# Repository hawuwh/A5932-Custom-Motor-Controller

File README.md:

# Custom Motor Controller using A5932 for LBYEC3H Solar Car Project

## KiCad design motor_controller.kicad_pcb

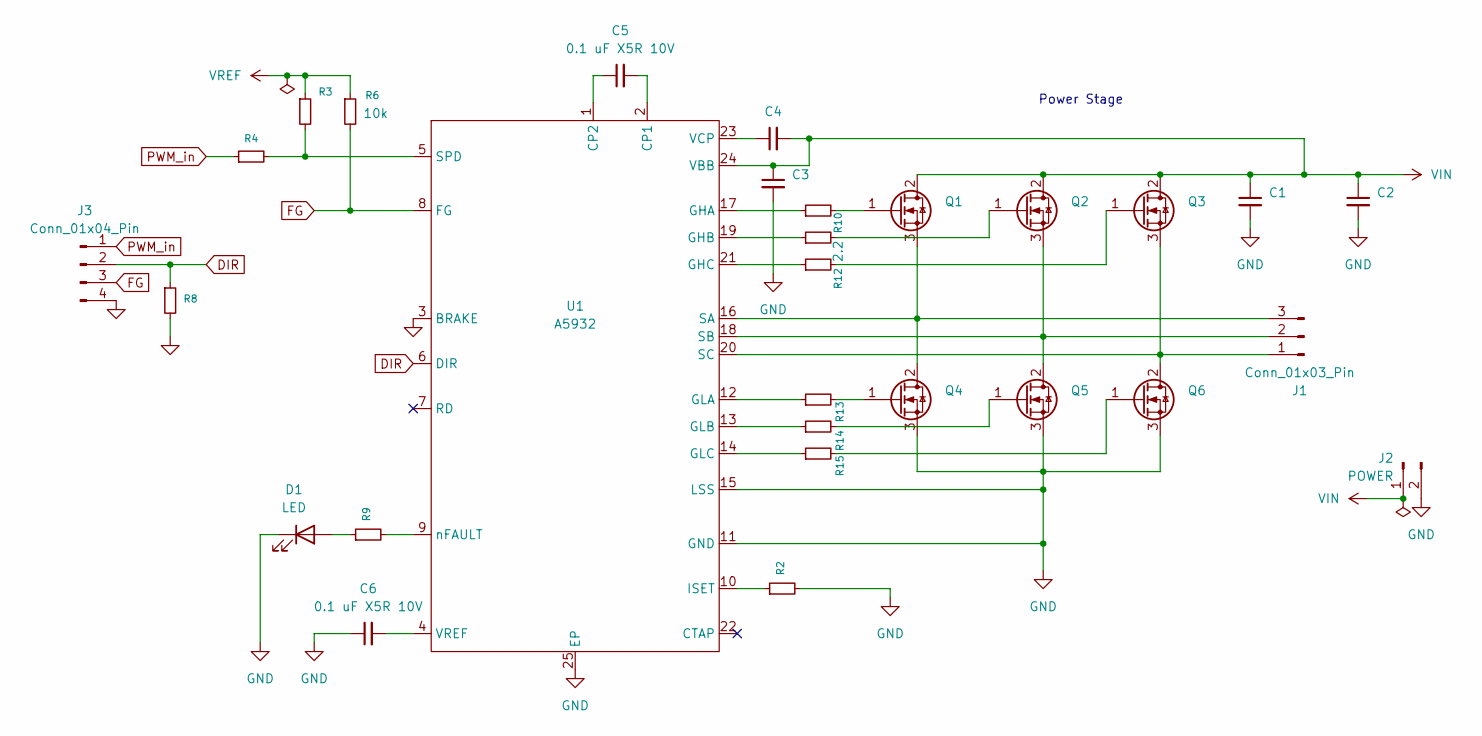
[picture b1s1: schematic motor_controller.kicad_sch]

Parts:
C1, C2: 100u; C_Radial_D5.0mm_H7.0mm_P2.00mm
C3, C4: C_Small; C_0805_2012Metric_Pad1.18x1.45mm_HandSolder
C5, C6: 0.1 uF X5R 10V; C_0805_2012Metric_Pad1.18x1.45mm_HandSolder
D1: LED; LED_D5.0mm
J1: Conn_01x03_Pin; TerminalBlock_Phoenix_MKDS-1,5-3-5.08_1x03_P5.08mm_Horizont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
J2: POWER; TerminalBlock_Phoenix_MKDS-1,5-2-5.08_1x02_P5.08mm_Horizont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
J3: Conn_01x04_Pin; PinSocket_1x04_P2.54mm_Vertical
Q1, Q2, Q3, Q4, Q5, Q6: IPP040N06NF2S; TO-220-3_Vertical
R2: 30k; R_Axial_DIN0207_L6.3mm_D2.5mm_P7.62mm_Horizontal
R3, R6, R8: 10k; R_Axial_DIN0207_L6.3mm_D2.5mm_P7.62mm_Horizontal
R4: 220; R_Axial_DIN0207_L6.3mm_D2.5mm_P7.62mm_Horizontal
R9: 330; R_Axial_DIN0207_L6.3mm_D2.5mm_P7.62mm_Horizontal
R10, R11, R12, R13, R14, R15: 2.2; R_Axial_DIN0207_L6.3mm_D2.5mm_P7.62mm_Horizontal
U1: A5932; HTSSOP-24-1EP_4.4x7.8mm_P0.65mm_EP3.4x4.75mm_Mask2.4x2.98mm

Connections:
DIR: J3.2, R8.1, U1.6 (DIR)
FG: J3.3, R6.2, U1.8 (FG)
GND: C1.2, C2.2, C3.2, C6.1, D1.1 (K), J2.2, J3.4, Q4.3 (S), Q5.3 (S), Q6.3 (S), R2.2, R8.2, U1.3 (BRAKE), U1.11 (GND), U1.15 (LSS), U1.25 (EP)
unnamed: D1.2 (A), R9.1
unnamed: J1.1, Q3.3 (S), Q6.2 (D), U1.20 (SC)
unnamed: J1.2, Q2.3 (S), Q5.2 (D), U1.18 (SB)
unnamed: J1.3, Q1.3 (S), Q4.2 (D), U1.16 (SA)
unnamed: Q1.1 (G), R10.2
unnamed: Q2.1 (G), R11.2
unnamed: Q3.1 (G), R12.2
unnamed: Q4.1 (G), R13.2
unnamed: Q5.1 (G), R14.2
unnamed: Q6.1 (G), R15.2
unnamed: C5.2, U1.2 (CP1)
unnamed: C5.1, U1.1 (CP2)
unnamed: R10.1, U1.17 (GHA)
unnamed: R11.1, U1.19 (GHB)
unnamed: R12.1, U1.21 (GHC)
unnamed: R13.1, U1.12 (GLA)
unnamed: R14.1, U1.13 (GLB)
unnamed: R15.1, U1.14 (GLC)
unnamed: R2.1, U1.10 (ISET)
unnamed: R3.2, R4.2, U1.5 (SPD)
unnamed: C4.1, U1.23 (VCP)
unnamed: R9.2, U1.9 (nFAULT)
PWM_in: J3.1, R4.1
VIN: C1.1, C2.1, C3.1, C4.2, J2.1, Q1.2 (D), Q2.2 (D), Q3.2 (D), U1.24 (VBB)

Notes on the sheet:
Power Stage

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
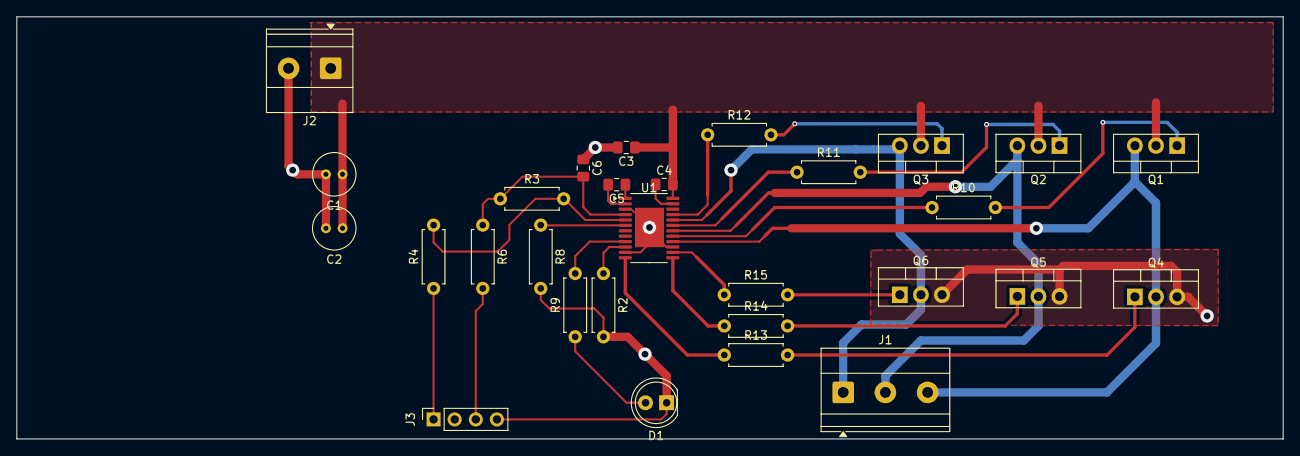
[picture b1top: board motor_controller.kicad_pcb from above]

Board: 2 copper layers, 152.4 x 50.8 mm, 29 parts (0 on the bottom side), 28 nets.
